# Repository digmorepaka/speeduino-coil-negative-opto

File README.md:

# Uses
This is a module meant to slot into any standard speeduino v0.3, v0.4, and NO2C boards. 
It uses the normal trigger signal conditioner pinout. 
It is ideal for use in a coil negative trigger setup, for example for a car like Suzuki Samurai.

# Single channel
Single channel version only conditions VR1+. ECM jumpers should be configured the same as for VR operation routing the trigger singal into the conditioner module.

# Dual Channel
Same as single channel but for both VR1+ and VR2+ pins. VRx- pins are no connect.
No idea where this would be useful but it's a thing.
~~PCB coming soon~~

#Design

The schematic is originally designed by megasquirt, this is an adapted layout for speeduino's vr conditioner module footprint

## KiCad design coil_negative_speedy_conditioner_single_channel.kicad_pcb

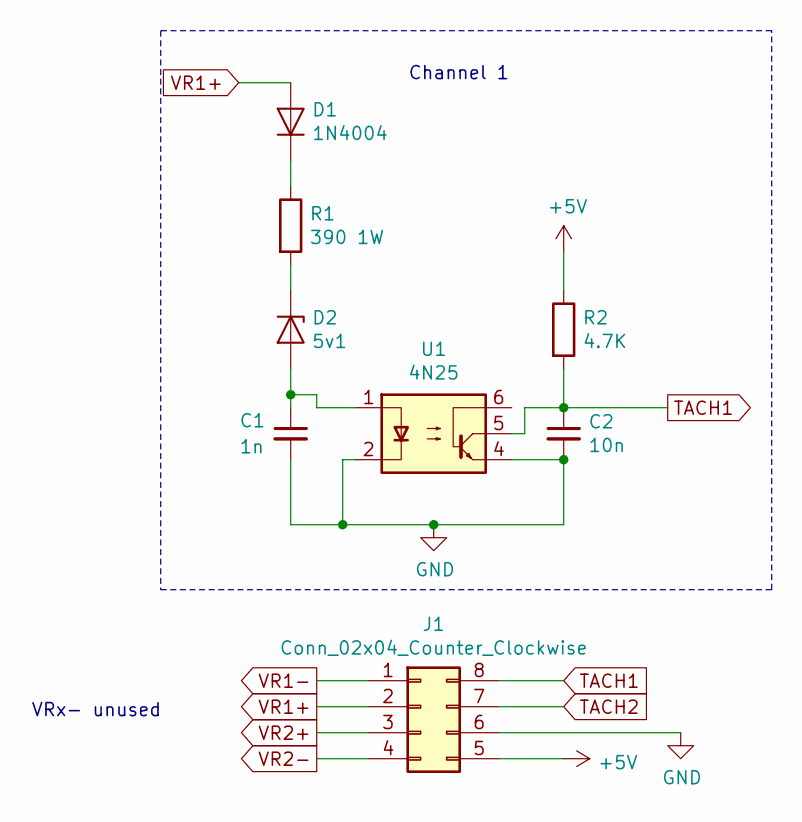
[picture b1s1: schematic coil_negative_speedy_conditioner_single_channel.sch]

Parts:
C1: 1n; C_Disc_D4.7mm_W2.5mm_P5.00mm
C2: 10n; C_Disc_D5.0mm_W2.5mm_P2.50mm
D1: 1N4004; D_DO-35_SOD27_P2.54mm_Vertical_AnodeUp
D2: 5v1; D_DO-35_SOD27_P2.54mm_Vertical_AnodeUp
J1: Conn_02x04_Counter_Clockwise; DIP-8_W7.62mm_LongPads
R1: 390 1W; R_Axial_DIN0414_L11.9mm_D4.5mm_P5.08mm_Vertical
R2: 4.7K; R_Axial_DIN0207_L6.3mm_D2.5mm_P2.54mm_Vertical
U1: 4N25; DIP-6_W7.62mm

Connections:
+5V: J1.5, R2.1
GND: C1.2, C2.2, J1.6, U1.2, U1.4
unnamed: C1.1, D2.2 (A), U1.1
unnamed: D1.1 (K), R1.1
unnamed: D2.1 (K), R1.2
TACH1: C2.1, J1.8, R2.2, U1.5
TACH2: J1.7
VR1+: D1.2 (A), J1.2
VR1-: J1.1
VR2+: J1.3
VR2-: J1.4

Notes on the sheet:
Channel 1
VRx- unused

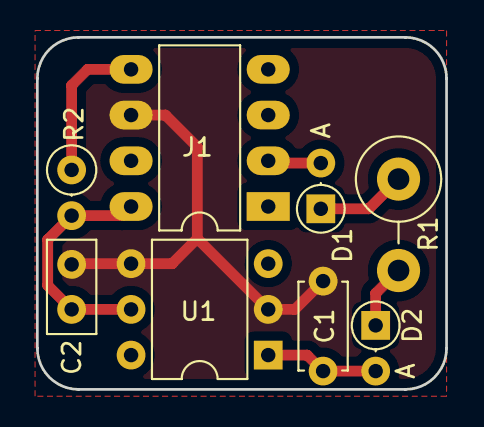
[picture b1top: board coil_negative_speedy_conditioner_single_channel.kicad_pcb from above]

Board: 2 copper layers, 22.7 x 19.6 mm, 8 parts (0 on the bottom side), 7 nets.

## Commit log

2021-03-12 add license
2021-03-12 add pdf schematic
2021-03-12 update pcb details
2021-03-26 VCC and GND flipped around
